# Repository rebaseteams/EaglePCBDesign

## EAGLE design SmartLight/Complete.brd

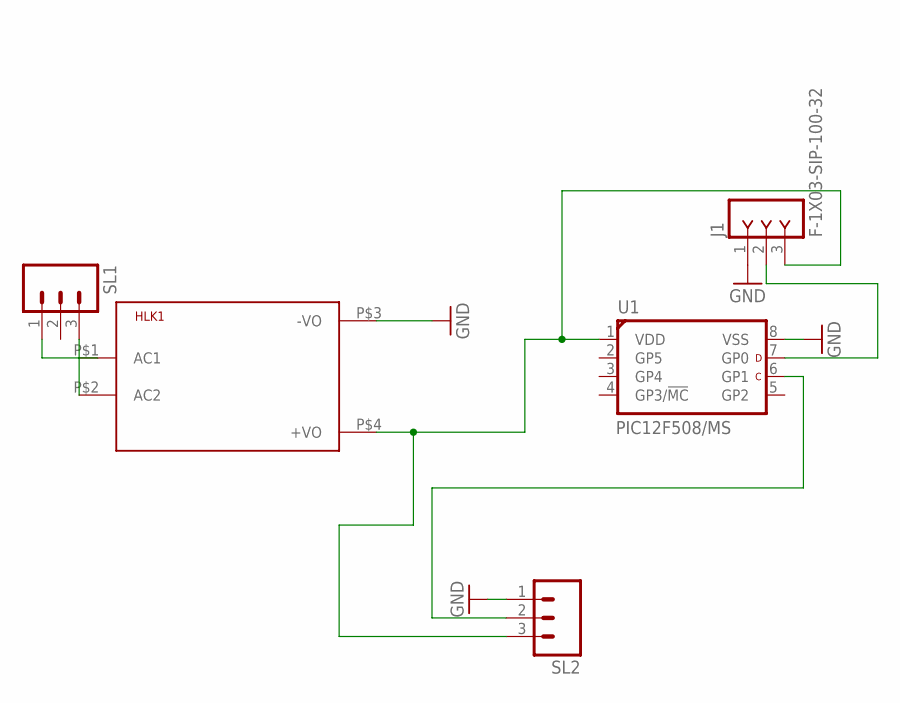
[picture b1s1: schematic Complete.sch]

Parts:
HLK1: HLK-PM013W; HLK-PM01
J1: F-1X03-SIP-100-32; SIP-100-03-32
SL1, SL2: M03; 03P
U1: PIC12F508/MS; MSOP8-MS

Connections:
GND: HLK1.P$3 (-VO), J1.1, SL2.1, U1.8 (VSS)
unnamed: J1.2, U1.7 (GP0)
unnamed: SL2.2, U1.6 (GP1)
unnamed: HLK1.P$1 (AC1), SL1.1
unnamed: HLK1.P$2 (AC2), SL1.3
unnamed: HLK1.P$4 (+VO), J1.3, SL2.3, U1.1 (VDD)

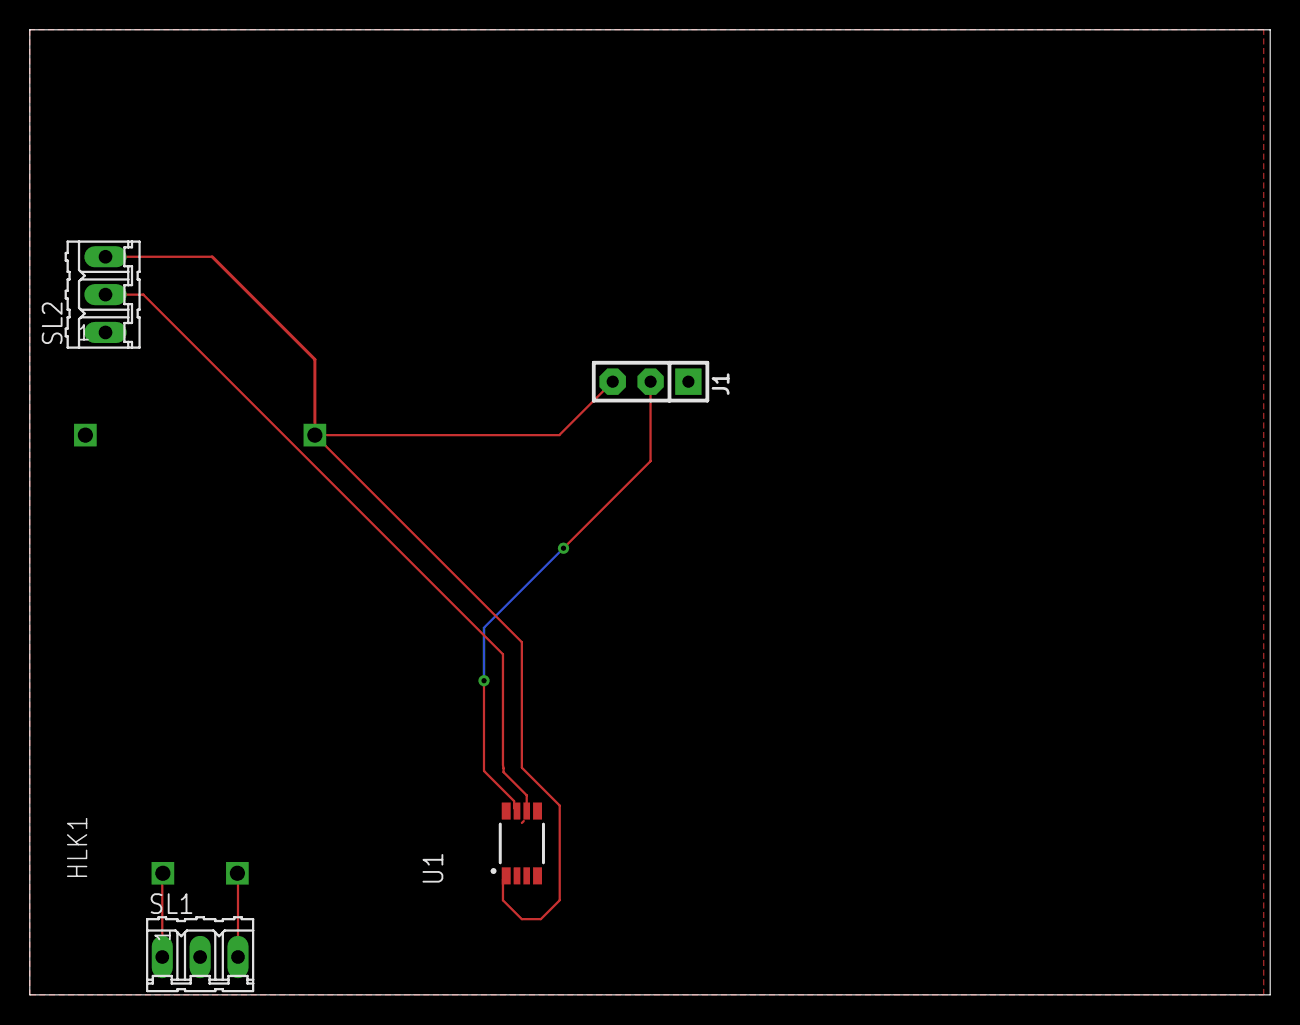
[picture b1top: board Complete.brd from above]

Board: 2 copper layers, 83.2 x 64.8 mm, 5 parts (0 on the bottom side), 6 nets.

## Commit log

2021-12-30 Changed file structure

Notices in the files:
parts and their libraries:
con-headers-jp: Copyright (C) 2008, Bob Starr
